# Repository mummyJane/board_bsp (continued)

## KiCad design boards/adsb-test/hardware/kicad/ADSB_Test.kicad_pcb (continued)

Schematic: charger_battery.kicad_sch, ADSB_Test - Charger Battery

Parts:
BT301: CR1220 (optional); Battery_Panasonic_CR1220-VCN_Vertical_CircularHoles; not fitted
C301, C302: 47nF; C_0805_2012Metric_Pad1.18x1.45mm_HandSolder
C303, C304, C305, C306, C307, C310, C311, C312, C313, C314, C316, C317: 10uF 25V; C_0805_2012Metric_Pad1.18x1.45mm_HandSolder
C308, C315: 100nF 25V; C_0805_2012Metric_Pad1.18x1.45mm_HandSolder
C309: 4.7uF 10V; C_0805_2012Metric_Pad1.18x1.45mm_HandSolder
C318: 1nF 50V; C_0805_2012Metric_Pad1.18x1.45mm_HandSolder
C319: 1uF 25V; C_0805_2012Metric_Pad1.18x1.45mm_HandSolder
C320, C321: 1uF; C_0805_2012Metric_Pad1.18x1.45mm_HandSolder
D301: CHG (amber); LED_0805_2012Metric_Pad1.15x1.40mm_HandSolder
D302: BAT43W; D_SOD-123
D303: BAT43W; D_SOD-123; not fitted
J301: 2S Li-ion pack (BAT+, GND, NTC); JST_XH_B3B-XH-A_1x03_P2.50mm_Vertical
L301: 2.2uH; L_Bourns_SRP7028A_7.3x6.6mm
R301: 8.2k 1%; R_0805_2012Metric_Pad1.20x1.40mm_HandSolder
R302: 10k; R_0805_2012Metric_Pad1.20x1.40mm_HandSolder
R303: 5.23k 1%; R_0805_2012Metric_Pad1.20x1.40mm_HandSolder
R304: 30.1k 1%; R_0805_2012Metric_Pad1.20x1.40mm_HandSolder
R305: 100R; R_0805_2012Metric_Pad1.20x1.40mm_HandSolder
R306: 2.2k; R_0805_2012Metric_Pad1.20x1.40mm_HandSolder
RS301, RS302: 20m; R_Shunt_1206_Kelvin_HandSolder
TP301: CHG_QON; TestPoint_Pad_D1.5mm
TP302: BAT_PACK; TestPoint_Pad_D1.5mm
TP303: VSYS; TestPoint_Pad_D1.5mm
TP304: VBUS_CHG; TestPoint_Pad_D1.5mm
TP305: VBACKUP; TestPoint_Pad_D1.5mm
U301: BQ25798; Texas_RQM0029A_VQFN-29_4x4mm_P0.4mm
U302: MCP1703 3.0V (2 uA Iq); SOT-23_Handsoldering

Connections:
/Charger Battery/BKP_CELL: BT301.1 (+), D303.2 (A)
/Charger Battery/CHG_BATP: R305.1, U301.18 (BATP)
/Charger Battery/CHG_BTST1: C301.1, U301.4 (BTST1)
/Charger Battery/CHG_BTST2: C302.1, U301.19 (BTST2)
/Charger Battery/CHG_CE: R302.1, U301.13 (~CE)
/Charger Battery/CHG_LED_A: D301.2 (A), R306.2
/Charger Battery/CHG_PMID: C305.1, C306.1, C307.1, C308.1, U301.29 (PMID)
/Charger Battery/CHG_PROG: R301.1, U301.20 (PROG)
/Charger Battery/CHG_QON: TP301.1, U301.12 (~QON)
/Charger Battery/CHG_REGN: C309.1, R303.1, R306.1, U301.5 (REGN), U301.17 (ILIM_HIZ)
/Charger Battery/CHG_SDRV: C318.1, U301.24 (SDRV)
/Charger Battery/CHG_STAT: D301.1 (K), U301.1 (STAT)
/Charger Battery/CHG_SW1: C301.2, L301.1, U301.28 (SW1)
/Charger Battery/CHG_SW2: C302.2, L301.2, U301.26 (SW2)
/Charger Battery/CHG_TS: J301.3, R303.2, R304.1, U301.16 (TS)
/Charger Battery/VBACKUP_LDO: C320.1, D302.2 (A), U302.2 (VO)
/Charger Battery/VBAT_CHG: C316.1, C317.1, RS301.1, U301.22 (BAT), U301.23 (BAT)
/Charger Battery/VSYS_CHG: C310.1, C311.1, C312.1, C313.1, C314.1, C315.1, RS302.1, U301.25 (SYS)
BAT_PACK: J301.1, R305.2, RS301.4, TP302.1
CHG_PD_INT: U301.21 (~INT); also elsewhere on the board
GND: BT301.2 (-), C303.2, C304.2, C305.2, C306.2, C307.2, C308.2, C309.2, C310.2, C311.2, C312.2, C313.2, C314.2, C315.2, C316.2, C317.2, C318.2, C319.2, C320.2, C321.2, J301.2, R301.2, R302.2, R304.2, U301.10 (ACDRV2), U301.11 (ACDRV1), U301.27 (GND), U302.1 (GND); also elsewhere on the board
I2C_SCL: U301.14 (SCL); also elsewhere on the board
I2C_SDA: U301.15 (SDA); also elsewhere on the board
PM1_CH2_N: RS301.3; also elsewhere on the board
PM1_CH2_P: RS301.2; also elsewhere on the board
PM1_CH3_N: RS302.3; also elsewhere on the board
PM1_CH3_P: RS302.2; also elsewhere on the board
VBACKUP: C321.1, D302.1 (K), D303.1 (K), TP305.1; also elsewhere on the board
VBUS_CHG: C303.1, C304.1, TP304.1, U301.2 (VBUS), U301.3 (VBUS), U301.8 (VAC2), U301.9 (VAC1); also elsewhere on the board
VSYS: C319.1, RS302.4, TP303.1, U302.3 (VI); also elsewhere on the board

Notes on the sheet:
CHARGER: BQ25798 buck-boost 2S charger + power path (I2C 0x6B), PROG 8.2k = 2S / 750 kHz, TS divider 5.23k/30.1k (10k NTC). Pack: 2 x 18650 with its own 2S protection + balancing on J301. RS301 VBAT (PM1 CH2, bidirectional), RS302 VSYS (PM1 CH3). VBACKUP: MCP1703 3.0 V (2 uA) from VSYS -> BAT43W ->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

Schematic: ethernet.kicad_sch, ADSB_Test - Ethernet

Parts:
C801, C803: 10uF; C_1206_3216Metric_Pad1.33x1.80mm_HandSolder
C802, C804, C805: 100nF; C_0805_2012Metric_Pad1.18x1.45mm_HandSolder
C806: 1uF; C_0805_2012Metric_Pad1.18x1.45mm_HandSolder
C807: 470pF; C_0805_2012Metric_Pad1.18x1.45mm_HandSolder
C808, C809: 27pF; C_0805_2012Metric_Pad1.18x1.45mm_HandSolder
C810: 22nF; C_0805_2012Metric_Pad1.18x1.45mm_HandSolder
FB801: 600R@100MHz; L_0805_2012Metric_Pad1.05x1.20mm_HandSolder
J801: HR911105A; RJ45_Hanrun_HR911105A_Horizontal
R801: 12.1k 1%; R_0805_2012Metric_Pad1.20x1.40mm_HandSolder
R802, R803, R804, R806, R814, R815, R816: 10k; R_0805_2012Metric_Pad1.20x1.40mm_HandSolder
R805: 1.5k; R_0805_2012Metric_Pad1.20x1.40mm_HandSolder
R807: 33R; R_0805_2012Metric_Pad1.20x1.40mm_HandSolder
R808, R809, R810, R811: 49.9R 1%; R_0805_2012Metric_Pad1.20x1.40mm_HandSolder
R812, R813: 270R; R_0805_2012Metric_Pad1.20x1.40mm_HandSolder
TP801: ETH_REF_CLK; TestPoint_Pad_D1.5mm
TP802: ETH_1V2; TestPoint_Pad_D1.5mm
U801: LAN8720A; VQFN-24-1EP_4x4mm_P0.5mm_EP2.5x2.5mm_HandSolder
Y801: 25MHz; Crystal_SMD_5032-2Pin_5.0x3.2mm_HandSoldering

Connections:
3V3_ETH: C801.1, C802.1, FB801.1, R804.1, R805.1, R806.1, R814.1, R815.1, R816.1, U801.9 (VDDIO); also elsewhere on the board
/Ethernet/ETH_1V2: C806.1, C807.1, TP802.1, U801.6 (VDDCR)
/Ethernet/ETH_AVDD: C803.1, C804.1, C805.1, C810.1, FB801.2, J801.4 (TCT), J801.5 (RCT), R808.1, R809.1, R810.1, R811.1, U801.1 (VDD2A), U801.19 (VDD1A)
/Ethernet/ETH_LED1: R802.1, R812.1, U801.3 (LED1/REGOFF)
/Ethernet/ETH_LED1_K: J801.12, R812.2
/Ethernet/ETH_LED2: R803.1, R813.1, U801.2 (LED2/~INTSEL)
/Ethernet/ETH_LED2_K: J801.9, R813.2
/Ethernet/ETH_RBIAS: R801.1, U801.24 (RBIAS)
/Ethernet/ETH_REFCLKO: R807.1, U801.14 (~INT/REFCLKO)
/Ethernet/ETH_RXER: R804.2, U801.10 (RXER/PHYAD0)
/Ethernet/ETH_RX_N: J801.6 (RD-), R811.2, U801.22 (RXN)
/Ethernet/ETH_RX_P: J801.3 (RD+), R810.2, U801.23 (RXP)
/Ethernet/ETH_TX_N: J801.2 (TD-), R809.2, U801.20 (TXN)
/Ethernet/ETH_TX_P: J801.1 (TD+), R808.2, U801.21 (TXP)
/Ethernet/ETH_XI: C808.1, U801.5 (XTAL1/CLKIN), Y801.1
/Ethernet/ETH_XO: C809.1, U801.4 (XTAL2), Y801.2
ETH_CRS_DV: R816.2, U801.11 (CRS_DV/MODE2); also elsewhere on the board
ETH_MDC: U801.13 (MDC); also elsewhere on the board
ETH_MDIO: R805.2, U801.12 (MDIO); also elsewhere on the board
ETH_PHY_RST: R806.2, U801.15 (~RST); also elsewhere on the board
ETH_REF_CLK: R807.2, TP801.1; also elsewhere on the board
ETH_RXD0: R814.2, U801.8 (RXD0/MODE0); also elsewhere on the board
ETH_RXD1: R815.2, U801.7 (RXD1/MODE1); also elsewhere on the board
ETH_TXD0: U801.17 (TXD0); also elsewhere on the board
ETH_TXD1_BOOT: U801.18 (TXD1); also elsewhere on the board
ETH_TX_EN: U801.16 (TXEN); also elsewhere on the board
GND: C801.2, C802.2, C803.2, C804.2, C805.2, C806.2, C807.2, C808.2, C809.2, C810.2, J801.8, J801.10, J801.11, J801.SH, R801.2, R802.2, R803.2, U801.25 (VSS); also elsewhere on the board

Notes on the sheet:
ETHERNET: LAN8720A 10/100 RMII PHY (replaces the IP101GRI: KiCad symbol, ESP-IDF lan87xx driver, cheap breakouts for Phase 1). 25 MHz crystal; REFCLKO (pin 14) feeds the P4 REF_CLK in (GPIO50) through 33R. Straps: REGOFF=0 (int. 1V2 on), nINTSEL=0 (REFCLKO, 10k pull-down), PHYAD0=1 (address 1), MOD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

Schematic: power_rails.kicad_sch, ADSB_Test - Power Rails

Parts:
C411, C412, C421, C422: 10uF 25V; C_0805_2012Metric_Pad1.18x1.45mm_HandSolder
C413, C415, C423, C425: 100nF; C_0805_2012Metric_Pad1.18x1.45mm_HandSolder
C414, C424: 33nF; C_0805_2012Metric_Pad1.18x1.45mm_HandSolder
C416, C417, C426, C427: 22uF 10V; C_1206_3216Metric_Pad1.33x1.80mm_HandSolder
C430, C431, C432, C433: 1nF; C_0805_2012Metric_Pad1.18x1.45mm_HandSolder
L411, L421: 4.7uH; L_Bourns_SRP5030T
R411: 100k; R_0805_2012Metric_Pad1.20x1.40mm_HandSolder
R412: 28k; R_0805_2012Metric_Pad1.20x1.40mm_HandSolder
R413: 52.3k 1%; R_0805_2012Metric_Pad1.20x1.40mm_HandSolder
R414, R424: 10k 1%; R_0805_2012Metric_Pad1.20x1.40mm_HandSolder
R423: 31.6k 1%; R_0805_2012Metric_Pad1.20x1.40mm_HandSolder
R430, R431, R432, R433: 100R; R_0805_2012Metric_Pad1.20x1.40mm_HandSolder
RS401: 30m; R_Shunt_1206_Kelvin_HandSolder
RS402, RS403, RS404: 50m; R_Shunt_1206_Kelvin_HandSolder
RS405: 330m; R_Shunt_1206_Kelvin_HandSolder
RS406, RS407: 1R; R_Shunt_1206_Kelvin_HandSolder
RS408, RS409: 2.2R; R_Shunt_1206_Kelvin_HandSolder
SW401: POWER (slide); SW_Slide_SPDT_Angled_CK_OS102011MA1Q
TP401: 5V; TestPoint_Pad_D1.5mm
TP402: 3V3; TestPoint_Pad_D1.5mm
TP403: VSYS; TestPoint_Pad_D1.5mm
TP410: 5V_SDR; TestPoint_Pad_D1.5mm
TP411: 5V_LCD; TestPoint_Pad_D1.5mm
TP412: 3V3_MCU; TestPoint_Pad_D1.5mm
TP413: 3V3_SD; TestPoint_Pad_D1.5mm
TP414: 3V3_ETH; TestPoint_Pad_D1.5mm
TP415: 3V3_GPS; TestPoint_Pad_D1.5mm
TP416: 3V3_M1421; TestPoint_Pad_D1.5mm
TP417: 3V3_PERIPH; TestPoint_Pad_D1.5mm
U411, U421: TPS62933; SOT-583-8_HandSolder
U430, U431, U432, U433: TPS22917; SOT-23-6_Handsoldering

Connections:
3V3: RS401.4, RS404.1, RS405.1, RS406.1, RS407.1, RS408.1, RS409.1, TP402.1; also elsewhere on the board
3V3_BUCK: C426.1, C427.1, L421.2, R423.1, RS401.1
3V3_ETH: R431.2, TP414.1, U431.6 (VOUT); also elsewhere on the board
3V3_GPS: R432.2, TP415.1, U432.6 (VOUT); also elsewhere on the board
3V3_M1421: R433.2, TP416.1, U433.6 (VOUT); also elsewhere on the board
3V3_MCU: RS404.4, TP412.1; also elsewhere on the board
3V3_PERIPH: RS409.4, TP417.1; also elsewhere on the board
3V3_SD: RS405.4, TP413.1; also elsewhere on the board
5V: C416.1, C417.1, L411.2, R413.1, RS402.1, RS403.1, TP401.1
5V_LCD: R430.2, TP411.1, U430.6 (VOUT); also elsewhere on the board
5V_SDR: RS402.4, TP410.1; also elsewhere on the board
/Power Rails/3V3_ETH_SH: RS406.4, U431.1 (VIN)
/Power Rails/3V3_GPS_SH: RS407.4, U432.1 (VIN)
/Power Rails/3V3_M1421_SH: RS408.4, U433.1 (VIN)
/Power Rails/5V_LCD_SH: RS403.4, U430.1 (VIN)
/Power Rails/B3V3_BST: C425.1, U421.6 (BST)
/Power Rails/B3V3_FB: R423.2, R424.1, U421.8 (FB)
/Power Rails/B3V3_SS: C424.1, U421.7 (SS)
/Power Rails/B3V3_SW: C425.2, L421.1, U421.5 (SW)
/Power Rails/B5V_BST: C415.1, U411.6 (BST)
/Power Rails/B5V_FB: R413.2, R414.1, U411.8 (FB)
/Power Rails/B5V_SS: C414.1, U411.7 (SS)
/Power Rails/B5V_SW: C415.2, L411.1, U411.5 (SW)
/Power Rails/CT30: C430.1, U430.4 (CT)
/Power Rails/CT31: C431.1, U431.4 (CT)
/Power Rails/CT32: C432.1, U432.4 (CT)
/Power Rails/CT33: C433.1, U433.4 (CT)
/Power Rails/PWR_EN: R411.2, R412.1, SW401.2 (B), U411.2 (EN), U421.2 (EN)
/Power Rails/QD30: R430.1, U430.5 (QOD)
/Power Rails/QD31: R431.1, U431.5 (QOD)
/Power Rails/QD32: R432.1, U432.5 (QOD)
/Power Rails/QD33: R433.1, U433.5 (QOD)
EXP_EN_ETH: U431.3 (ON); also elsewhere on the board
EXP_EN_GPS: U432.3 (ON); also elsewhere on the board
EXP_EN_LCD: U430.3 (ON); also elsewhere on the board
EXP_EN_M1421: U433.3 (ON); also elsewhere on the board
GND: C411.2, C412.2, C413.2, C414.2, C416.2, C417.2, C421.2, C422.2, C423.2, C424.2, C426.2, C427.2, C430.2, C431.2, C432.2, C433.2, R412.2, R414.2, R424.2, SW401.3 (C), U411.4 (GND), U421.4 (GND), U430.2 (GND), U431.2 (GND), U432.2 (GND), U433.2 (GND); also elsewhere on the board
PM1_CH4_N: RS402.3; also elsewhere on the board
PM1_CH4_P: RS402.2; also elsewhere on the board
PM2_CH1_N: RS403.3; also elsewhere on the board
PM2_CH1_P: RS403.2; also elsewhere on the board
PM2_CH2_N: RS404.3; also elsewhere on the board
PM2_CH2_P: RS404.2; also elsewhere on the board
PM2_CH3_N: RS405.3; also elsewhere on the board
PM2_CH3_P: RS405.2; also elsewhere on the board
PM2_CH4_N: RS406.3; also elsewhere on the board
PM2_CH4_P: RS406.2; also elsewhere on the board
PM3_CH1_N: RS407.3; also elsewhere on the board
PM3_CH1_P: RS407.2; also elsewhere on the board
PM3_CH2_N: RS408.3; also elsewhere on the board
PM3_CH2_P: RS408.2; also elsewhere on the board
PM3_CH3_N: RS409.3; also elsewhere on the board
PM3_CH3_P: RS409.2; also elsewhere on the board
PM3_CH4_N: RS401.3; also elsewhere on the board
PM3_CH4_P: RS401.2; also elsewhere on the board
VSYS: C411.1, C412.1, C413.1, C421.1, C422.1, C423.1, R411.1, TP403.1, U411.3 (VIN), U421.3 (VIN); also elsewhere on the board

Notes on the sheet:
RAILS: two TPS62933 bucks from VSYS (5 V and 3V3, 3 A each), shared PWR_EN with UVLO ~5.5 V. Every branch has a Kelvin shunt (PAC1954 channel on its sense labels) that doubles as a bring-up link. TPS22917 load switches on 5V_LCD, 3V3_ETH, 3V3_GPS, 3V3_M1421 (enabled from the TCA6408A). 3V3_MCU feed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
POWER: SW401 OFF = PWR_EN low = both bucks off. VSYS, charger and VBACKUP stay alive.

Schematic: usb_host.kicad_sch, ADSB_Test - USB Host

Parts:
C1101: 10nF; C_0805_2012Metric_Pad1.18x1.45mm_HandSolder
C1102: 1uF; C_0805_2012Metric_Pad1.18x1.45mm_HandSolder
C1103: 150uF 10V; CP_Elec_6.3x5.8
C1104: 100nF; C_0805_2012Metric_Pad1.18x1.45mm_HandSolder
J1101: USB-A (SDR hub); USB_A_Wuerth_614004134726_Horizontal
R1101: 604R 1%; R_0805_2012Metric_Pad1.20x1.40mm_HandSolder
R1102: 402k 1%; R_0805_2012Metric_Pad1.20x1.40mm_HandSolder
R1103: 10k; R_0805_2012Metric_Pad1.20x1.40mm_HandSolder
R1104: 100k; R_0805_2012Metric_Pad1.20x1.40mm_HandSolder
TP1101: VBUS_HOST; TestPoint_Pad_D1.5mm
TP1102: USBA_FAULT; TestPoint_Pad_D1.5mm
U1101: TPS259621DDA; TI_SO-PowerPAD-8_ThermalVias
U1102: USBLC6-2SC6; SOT-23-6_Handsoldering

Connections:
3V3: R1103.1; also elsewhere on the board
5V_SDR: C1102.1, U1101.4 (VIN); also elsewhere on the board
/USB Host/USBA_DVDT: C1101.1, U1101.2 (dV/dT)
/USB Host/USBA_ILM: R1101.1, U1101.7 (ILM)
/USB Host/USBA_OVC: R1102.1, U1101.8 (OVLO/OVCSEL)
EXP_USBA_EN: R1104.1, U1101.3 (EN/UVLO); also elsewhere on the board
GND: C1101.2, C1102.2, C1103.2, C1104.2, J1101.4 (GND), J1101.SH (Shield), R1101.2, R1102.2, R1104.2, U1101.1 (GND), U1101.9 (GND), U1102.2 (GND); also elsewhere on the board
USBA_FAULT: R1103.2, TP1102.1, U1101.6 (~FLT); also elsewhere on the board
USB_HS_D_N: J1101.2 (D-), U1102.3 (I/O2), U1102.4 (I/O2); also elsewhere on the board
USB_HS_D_P: J1101.3 (D+), U1102.1 (I/O1), U1102.6 (I/O1); also elsewhere on the board
VBUS_HOST: C1103.1, C1104.1, J1101.1 (VBUS), TP1101.1, U1101.5 (OUT), U1102.5 (VBUS)

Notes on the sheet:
USB HOST: P4 HS OTG (module pads 44/45) -> USBLC6 -> USB-A, 90R differential, short. VBUS: 5V_SDR (shunt RS402, PM1 CH4) -> TPS259621 eFuse (~1.5 A, 5.7 V clamp, dV/dt 10 nF) -> 150 uF. EN from the expander (EXP_USBA_EN, 100k pull-down: off at reset), FAULT (open drain) -> P4 GPIO27. PowerPAD: ther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

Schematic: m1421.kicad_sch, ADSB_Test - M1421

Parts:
C1401: 1uF; C_0805_2012Metric_Pad1.18x1.45mm_HandSolder
C1402: 100nF; C_0805_2012Metric_Pad1.18x1.45mm_HandSolder
D1401: RED 1090; LED_0805_2012Metric_Pad1.15x1.40mm_HandSolder
D1402: GREEN UAT; LED_0805_2012Metric_Pad1.15x1.40mm_HandSolder
D1403: ESD7351XV2T1G; D_SOD-523
J1401: m1421 JTAG (J-Link); PinHeader_2x05_P1.27mm_Vertical_SMD
J1402: ADSBee 1421 Dev Kit; PinHeader_1x06_P2.54mm_Vertical
J1403: SMA 1090/978; SMA_Samtec_SMA-J-P-H-ST-EM1_EdgeMount
R1401, R1402, R1403, R1404, R1405, R1409: 100k; R_0805_2012Metric_Pad1.20x1.40mm_HandSolder
R1406: 287R; R_0805_2012Metric_Pad1.20x1.40mm_HandSolder
R1407: 115R; R_0805_2012Metric_Pad1.20x1.40mm_HandSolder
R1408: 100R; R_0805_2012Metric_Pad1.20x1.40mm_HandSolder
SH1401: RF can frame (DNP); Laird_Technologies_BMI-S-203-F_26.21x26.21mm; MPN Laird BMI-S-203-F frame + BMI-S-203-C l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; not fitted
TP1401: SD23; TestPoint_Pad_D1.5mm
TP1402: SD24; TestPoint_Pad_D1.5mm
TP1403: SD25; TestPoint_Pad_D1.5mm
TP1404: LD11; TestPoint_Pad_D1.5mm
TP1405: LD09; TestPoint_Pad_D1.5mm
TP1406: LD08; TestPoint_Pad_D1.5mm
TP1407: LRST; TestPoint_Pad_D1.5mm
TP1408: CSMI; TestPoint_Pad_D1.5mm
TP1409: CSMO; TestPoint_Pad_D1.5mm
TP1410: CSCK; TestPoint_Pad_D1.5mm
TP1411: LRCS; TestPoint_Pad_D1.5mm
TP1412: LBSY; TestPoint_Pad_D1.5mm
U1401: ADSBee m1421; PantsForBirds_ADSBee_m1421_Module_HandSolder
U1402: 74LVC1G97 (AND); SOT-23-6_Handsoldering
U1403: 74LVC1G32; SOT-23-5_HandSoldering
U1404: 74LVC1G07; SOT-23-5_HandSoldering
U1405: SCN-2-11+; MiniCircuits_SCN

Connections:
3V3_M1421: C1401.1, C1402.1, J1401.1 (VTref), J1402.1, R1401.1, R1404.1, R1405.1, R1409.1, U1401.1 (VCC), U1401.4 (VCC), U1401.19 (VCC), U1401.22 (VCC), U1402.5 (VCC), U1403.5 (VCC), U1404.5 (VCC); also elsewhere on the board
/M1421/LED_SD26_A: D1401.2 (A), R1406.2
/M1421/LED_SD27_A: D1402.2 (A), R1407.2
/M1421/M1421_CSCK: TP1410.1, U1401.31 (COPRO_SPI_CLK)
/M1421/M1421_CSMI: TP1408.1, U1401.29 (COPRO_SPI_MISO)
/M1421/M1421_CSMO: TP1409.1, U1401.30 (COPRO_SPI_MOSI)
/M1421/M1421_LBSY: TP1412.1, U1401.33 (LR_BUSY)
/M1421/M1421_LD08: TP1406.1, U1401.5 (LR_DIO8)
/M1421/M1421_LD09: TP1405.1, U1401.3 (LR_DIO9)
/M1421/M1421_LD11: TP1404.1, U1401.2 (LR_DIO11)
/M1421/M1421_LRCS: TP1411.1, U1401.32 (~LR_CS)
/M1421/M1421_LRST: TP1407.1, U1401.7 (~LR_RESET)
/M1421/M1421_RF_978: R1408.2, U1401.24 (SUBG_RF), U1405.6 (P1)
/M1421/M1421_RF_1090: R1408.1, U1401.26 (LR_RF_LF), U1405.4 (P2)
/M1421/M1421_SD23: TP1401.1, U1401.12 (SUBG_DIO23)
/M1421/M1421_SD24: TP1402.1, U1401.13 (SUBG_DIO24)
/M1421/M1421_SD25: TP1403.1, U1401.14 (SUBG_DIO25)
/M1421/M1421_TCKC: J1401.4 (SWCLK/TCK), U1401.9 (JTAG_TCKC)
/M1421/M1421_TDI: J1401.8 (NC/TDI), U1401.11 (JTAG_TDI)
/M1421/M1421_TDO: J1401.6 (SWO/TDO), U1401.10 (JTAG_TDO)
/M1421/M1421_TMSC: J1401.2 (SWDIO/TMS), U1401.8 (JTAG_TMSC)
/M1421/RF_ADSB_ANT: D1403.1 (A1), J1403.1 (In), U1405.2 (SUM)
DEV_M1421_NRST: R1404.2, U1404.2; also elsewhere on the board
DEV_M1421_SYNC: R1403.1, U1403.2; also elsewhere on the board
DEV_M1421_TX: R1401.2, U1402.3 (IN0); also elsewhere on the board
GND: C1401.2, C1402.2, D1401.1 (K), D1402.1 (K), D1403.2 (A2), J1401.3 (GND), J1401.5 (GND), J1401.9 (GNDDetect), J1402.6, J1403.2 (Ext), R1402.2, R1403.2, SH1401.1, U1401.6 (GND), U1401.18 (GND), U1401.23 (GND), U1401.25 (GND), U1401.27 (GND), U1401.34 (GND), U1401.36 (GND), U1401.MP, U1402.1 (IN1), U1402.2 (GND), U1403.3 (GND), U1404.3 (GND), U1405.1 (GND), U1405.3 (GND), U1405.5 (GND); also elsewhere on the board
M1421_NRST: J1401.10 (~RESET), J1402.5, R1405.2, U1401.17 (~SUBG_RESET), U1404.4; also elsewhere on the board
M1421_SD26: R1406.1, U1401.15 (SUBG_DIO26); also elsewhere on the board
M1421_SD27: R1407.1, U1401.16 (SUBG_DIO27); also elsewhere on the board
M1421_SURX: J1402.2, U1401.20 (SUBG_UART_RX), U1402.4 (Y); also elsewhere on the board
M1421_SUTX: J1402.3, U1401.21 (SUBG_UART_TX); also elsewhere on the board
M1421_SYNC: J1402.4, R1402.1, U1401.28 (SYNC), U1403.4; also elsewhere on the board
P4_M1421_SYNC: U1403.1; also elsewhere on the board
P4_M1421_TX: R1409.2, U1402.6 (IN2); also elsewhere on the board

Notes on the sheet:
FIT OPTIONS: solder U1401 (m1421), or leave it off and plug the ADSBee 1421 Dev Kit into J1402 (JST-GH harness, own antenna). SYNC (pad 28) is an INPUT: high at reset = ROM bootloader, high at run time = sleep. SURX = P4 TX AND Dev TX (U1402). M1421_NRST: TCA6408A bit 7 (open-drain style), U1404 fo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

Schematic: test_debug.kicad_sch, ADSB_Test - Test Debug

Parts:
H1601, H1602, H1603, H1604: M2.5; MountingHole_2.7mm_M2.5_Pad_Via
J1601: Kingst LA5016 (2x20 keyed); IDC-Header_2x20_P2.54mm_Vertical
R1601, R1602, R1603, R1604, R1605, R1606, R1607, R1608, R1609, R1610, R1611, R1612, R1613, R1614, R1615, R1616: 100R; R_0805_2012Metric_Pad1.20x1.40mm_HandSolder
R1617: 0R; R_0805_2012Metric_Pad1.20x1.40mm_HandSolder; not fitted
TP1601: LA_PWM1; TestPoint_Pad_D1.5mm
TP1602: LA_PWM2; TestPoint_Pad_D1.5mm
TP1603, TP1604, TP1605, TP1606: GND; TestPoint_Pad_D1.5mm

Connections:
/Test Debug/LA_CH0: J1601.1, R1601.2
/Test Debug/LA_CH1: J1601.3, R1602.2
/Test Debug/LA_CH2: J1601.5, R1603.2
/Test Debug/LA_CH3: J1601.7, R1604.2
/Test Debug/LA_CH4: J1601.9, R1605.2
/Test Debug/LA_CH5: J1601.11, R1606.2
/Test Debug/LA_CH6: J1601.13, R1607.2
/Test Debug/LA_CH7: J1601.15, R1608.2
/Test Debug/LA_CH8: J1601.19, R1609.2
/Test Debug/LA_CH9: J1601.21, R1610.2
/Test Debug/LA_CH10: J1601.23, R1611.2
/Test Debug/LA_CH11: J1601.25, R1612.2
/Test Debug/LA_CH12: J1601.27, R1613.2
/Test Debug/LA_CH13: J1601.29, R1614.2
/Test Debug/LA_CH14: J1601.31, R1615.2
/Test Debug/LA_CH15: J1601.33, R1616.2
/Test Debug/LA_PWM1: J1601.37, R1617.1, TP1601.1
/Test Debug/LA_PWM2: J1601.39, TP1602.1
C5_CON_TX: R1610.1; also elsewhere on the board
CHG_PD_INT: R1614.1; also elsewhere on the board
DBG_A: R1615.1; also elsewhere on the board
DBG_B: R1616.1; also elsewhere on the board
GND: H1601.1, H1602.1, H1603.1, H1604.1, J1601.17, J1601.18, J1601.35, J1601.36, TP1603.1, TP1604.1, TP1605.1, TP1606.1; also elsewhere on the board
GPS_PPS: R1603.1, R1617.2; also elsewhere on the board
GPS_TX: R1604.1; also elsewhere on the board
I2C_SCL: R1601.1; also elsewhere on the board
I2C_SDA: R1602.1; also elsewhere on the board
M1421_SD26: R1608.1; also elsewhere on the board
M1421_SD27: R1612.1; also elsewhere on the board
M1421_SURX: R1606.1; also elsewhere on the board
M1421_SUTX: R1605.1; also elsewhere on the board
M1421_SYNC: R1607.1; also elsewhere on the board
P4_CON_TX: R1609.1; also elsewhere on the board
P4_USER_TX: R1611.1; also elsewhere on the board
PM_ALERT: R1613.1; also elsewhere on the board

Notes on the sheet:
LOGIC ANALYSER: Kingst LA5016 40-way cable into J1601. Key-side row (odd pins): 1-15 CH0-7, 17 GND, 19-33 CH8-15, 35 GND, 37 PWM1, 39 PWM2 (LA outputs). Even row reserved for the LA5032 (18/36 GND). CH: 0 SCL, 1 SDA, 2 GPS PPS, 3 GPS TX, 4 m1421 SUTX, 5 m1421 SURX, 6 SYNC, 7 SD26 | 8 P4 console TX,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

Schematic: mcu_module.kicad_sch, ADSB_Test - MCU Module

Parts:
C601, C602: 22uF 10V; C_1206_3216Metric_Pad1.33x1.80mm_HandSolder
C603, C608, C609: 100nF; C_0805_2012Metric_Pad1.18x1.45mm_HandSolder
C604, C607: 1uF; C_0805_2012Metric_Pad1.18x1.45mm_HandSolder
C605, C606: 22pF; C_0805_2012Metric_Pad1.18x1.45mm_HandSolder
J601: U.FL Wi-Fi (from module IPEX); U.FL_Hirose_U.FL-R-SMT-1_Vertical
J602: RP-SMA Wi-Fi 2.4/5 GHz; SMA_Molex_73251-3152_RP_EdgeMount; MPN Molex 0732513152 (RP-SMA, jam nut); foo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
R601: 10M; R_0805_2012Metric_Pad1.20x1.40mm_HandSolder
R602, R603: 2.2k; R_0805_2012Metric_Pad1.20x1.40mm_HandSolder
R604: 4.7k; R_0805_2012Metric_Pad1.20x1.40mm_HandSolder
R605, R607, R608: 10k; R_0805_2012Metric_Pad1.20x1.40mm_HandSolder
R606: 330R; R_0805_2012Metric_Pad1.20x1.40mm_HandSolder
R609: 470R; R_0805_2012Metric_Pad1.20x1.40mm_HandSolder
SW601: BOOT; SW_PUSH_6mm
SW602: RESET; SW_PUSH_6mm
SW603: SLEEP/WAKE; SW_Tactile_SPST_Angled_PTS645Vx31-2LFS
TP601: C5_IO27; TestPoint_Pad_D1.5mm
TP602: C5_IO25; TestPoint_Pad_D1.5mm
TP603: C5_IO24; TestPoint_Pad_D1.5mm
TP604: C5_IO23; TestPoint_Pad_D1.5mm
TP605: C5_IO6; TestPoint_Pad_D1.5mm
TP606: C5_IO5; TestPoint_Pad_D1.5mm
TP607: C5_IO4; TestPoint_Pad_D1.5mm
TP608: SLEEP_WAKE; TestPoint_Pad_D1.5mm
TP609: P4_GPIO20; TestPoint_Pad_D1.5mm
TP610: P4_GPIO36; TestPoint_Pad_D1.5mm
TP611: C5_PU; TestPoint_Pad_D1.5mm
U601: ESP32-P4C5 Core (OSPTEK); OSPTEK_ESP32-P4C5_Core_HandSolder
Y601: 32.768kHz; Crystal_C26-LF_D2.1mm_L6.5mm_Horizontal

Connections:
3V3: R602.1, R603.1, R604.1, R605.1; also elsewhere on the board
3V3_MCU: C601.1, C602.1, C603.1, R607.1, R608.1, U601.85 (ESP_3V3), U601.86 (ESP_3V3); also elsewhere on the board
/MCU Module/C5_IO4: TP607.1, U601.14 (C5_IO4)
/MCU Module/C5_IO5: TP606.1, U601.13 (C5_IO5)
/MCU Module/C5_IO6: TP605.1, U601.12 (C5_IO6)
/MCU Module/C5_IO23: TP604.1, U601.11 (C5_IO23)
/MCU Module/C5_IO24: TP603.1, U601.10 (C5_IO24)
/MCU Module/C5_IO25: TP602.1, U601.9 (C5_IO25)
/MCU Module/C5_IO26: R605.2, U601.8 (C5_IO26)
/MCU Module/C5_IO27: TP601.1, U601.7 (C5_IO27)
/MCU Module/C5_PU: R606.1, TP611.1, U601.82 (GPIO54/C5_CHIP_PU)
/MCU Module/P4_GPIO20: TP609.1, U601.29 (GPIO20)
/MCU Module/P4_GPIO36: TP610.1, U601.63 (GPIO36)
/MCU Module/SLEEP_BTN: R608.2, R609.1, SW603.1
/MCU Module/SLEEP_WAKE: C609.1, R609.2, TP608.1, U601.27 (GPIO12)
/MCU Module/WIFI_ANT: J601.1 (In), J602.1 (In)
/MCU Module/XTAL32_N: C606.1, R601.2, U601.88 (GPIO0/XTAL_32K_N), Y601.2
/MCU Module/XTAL32_P: C605.1, R601.1, U601.16 (GPIO1/XTAL_32K_P), Y601.1
C5_BOOT: U601.6 (C5_IO28/BOOT); also elsewhere on the board
C5_CON_RX: U601.4 (C5_U0RXD); also elsewhere on the board
C5_CON_TX: U601.5 (C5_U0TXD); also elsewhere on the board
C5_EN: R606.2; also elsewhere on the board
CHG_PD_INT: U601.24 (GPIO9); also elsewhere on the board
DBG_A: U601.25 (GPIO10); also elsewhere on the board
DBG_B: U601.26 (GPIO11); also elsewhere on the board
DSI_CLK_N: U601.36 (DSI_CLKN); also elsewhere on the board
DSI_CLK_P: U601.37 (DSI_CLKP); also elsewhere on the board
DSI_D0_N: U601.39 (DSI_D0N); also elsewhere on the board
DSI_D0_P: U601.38 (DSI_D0P); also elsewhere on the board
DSI_D1_N: U601.35 (DSI_D1N); also elsewhere on the board
DSI_D1_P: U601.34 (DSI_D1P); also elsewhere on the board
ETH_CRS_DV: U601.55 (GPIO28); also elsewhere on the board
ETH_MDC: U601.58 (GPIO31); also elsewhere on the board
ETH_MDIO: U601.80 (GPIO52); also elsewhere on the board
ETH_PHY_RST: U601.79 (GPIO51); also elsewhere on the board
ETH_REF_CLK: U601.78 (GPIO50); also elsewhere on the board
ETH_RXD0: U601.56 (GPIO29); also elsewhere on the board
ETH_RXD1: U601.57 (GPIO30); also elsewhere on the board
ETH_TXD0: U601.61 (GPIO34); also elsewhere on the board
ETH_TXD1_BOOT: R604.2, SW601.1, U601.62 (GPIO35/BOOT); also elsewhere on the board
ETH_TX_EN: U601.77 (GPIO49); also elsewhere on the board
EXP_INT: U601.81 (GPIO53); also elsewhere on the board
GND: C601.2, C602.2, C603.2, C604.2, C605.2, C606.2, C607.2, C608.2, C609.2, J601.2 (Ext), J602.2 (Ext), SW601.2, SW602.2, SW603.2, U601.1 (GND), U601.3 (GND), U601.15 (GND), U601.33 (GND), U601.40 (GND), U601.47 (GND), U601.52 (GND), U601.83 (GND); also elsewhere on the board
GPS_PPS: U601.19 (GPIO4); also elsewhere on the board
GPS_TX: U601.18 (GPIO3); also elsewhere on the board
I2C_SCL: R603.2, U601.23 (GPIO8); also elsewhere on the board
I2C_SDA: R602.2, U601.22 (GPIO7); also elsewhere on the board
LCD_BL_PWM: U601.59 (GPIO32); also elsewhere on the board
LCD_RST: U601.60 (GPIO33); also elsewhere on the board
M1421_SUTX: U601.75 (GPIO47); also elsewhere on the board
P4_CON_RX: U601.65 (GPIO38/U0RXD); also elsewhere on the board
P4_CON_TX: U601.64 (GPIO37/U0TXD); also elsewhere on the board
P4_EN: C607.1, R607.2, SW602.1, U601.87 (CHIP_PU); also elsewhere on the board
P4_GPS_TX: U601.17 (GPIO2); also elsewhere on the board
P4_M1421_SYNC: U601.76 (GPIO48); also elsewhere on the board
P4_M1421_TX: U601.74 (GPIO46); also elsewhere on the board
P4_USER_RX: U601.31 (GPIO22); also elsewhere on the board
P4_USER_TX: U601.30 (GPIO21); also elsewhere on the board
P4_USJ_D_N: U601.50 (GPIO24/USB_JTAG_N); also elsewhere on the board
P4_USJ_D_P: U601.51 (GPIO25/USB_JTAG_P); also elsewhere on the board
PM_ALERT: U601.20 (GPIO5); also elsewhere on the board
RTC_INT: U601.28 (GPIO13); also elsewhere on the board
SD_CLK: U601.71 (GPIO43); also elsewhere on the board
SD_CMD: U601.72 (GPIO44); also elsewhere on the board
SD_D0: U601.67 (GPIO39); also elsewhere on the board
SD_D1: U601.68 (GPIO40); also elsewhere on the board
SD_D2: U601.69 (GPIO41); also elsewhere on the board
SD_D3: U601.70 (GPIO42); also elsewhere on the board
SD_PWR_EN: U601.73 (GPIO45); also elsewhere on the board
SD_VIO: C604.1, U601.66 (ESP_LDO_VO4); also elsewhere on the board
TOUCH_INT: U601.53 (GPIO26); also elsewhere on the board
TOUCH_RST: U601.32 (GPIO23); also elsewhere on the board
USBA_FAULT: U601.54 (GPIO27); also elsewhere on the board
USB_HS_D_N: U601.48 (USB_DM); also elsewhere on the board
USB_HS_D_P: U601.49 (USB_DP); also elsewhere on the board
VBACKUP: C608.1, U601.84 (RTC_VBAT); also elsewhere on the board

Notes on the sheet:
MCU MODULE: OSPTEK ESP32-P4C5 Core (ESP32-P4 rev v3.x + ESP32-C5HF4, 16 MB flash, 32 MB PSRAM). Inside the module: SDIO on P4 GPIO14-19, C5 CHIP_PU = P4 GPIO54 (pad 82), C5 GPIO2 = P4 GPIO6 (pad 21, NC here) - the same wiring as the Waveshare reference board. Pins: bsp/include/bsp/board_pins.h. 3.3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

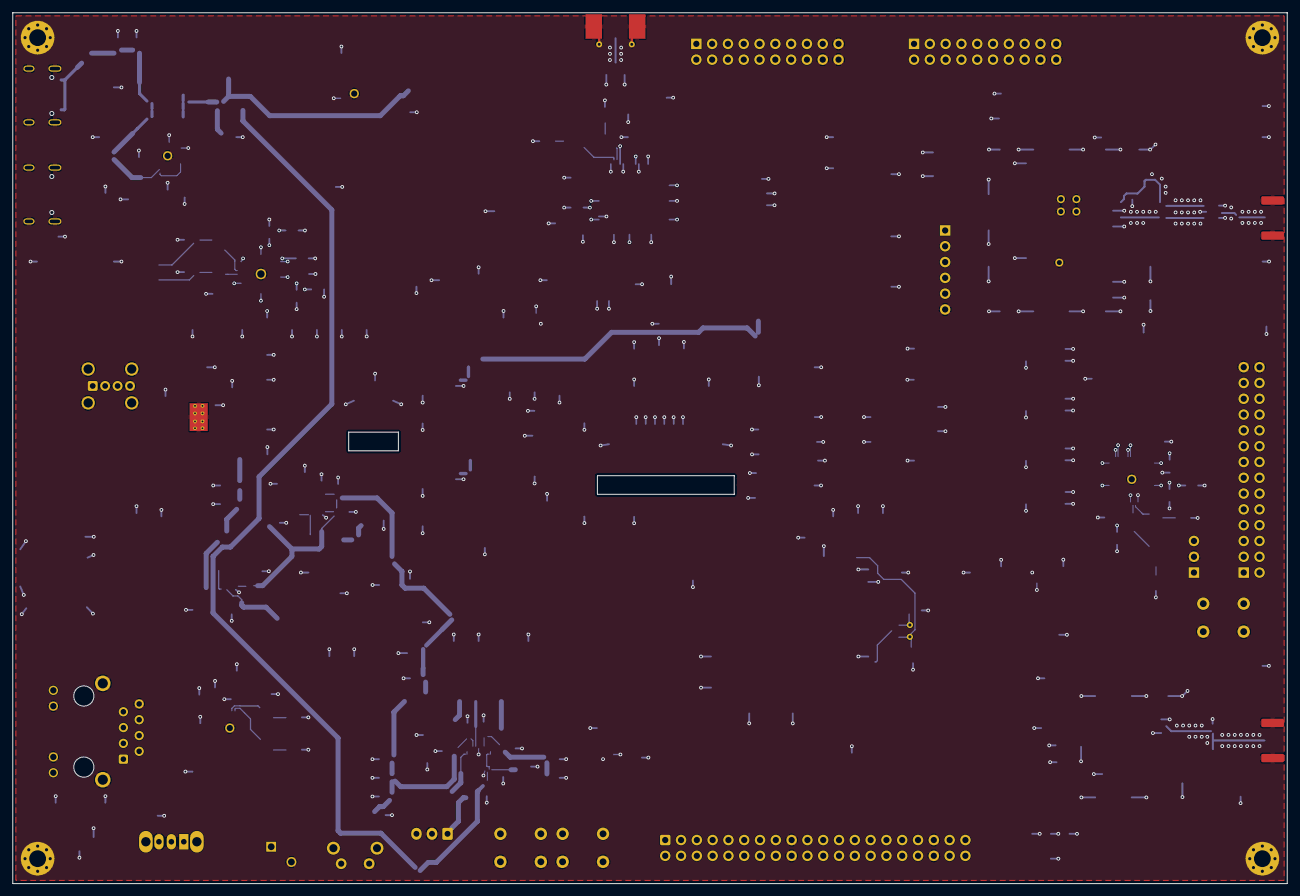
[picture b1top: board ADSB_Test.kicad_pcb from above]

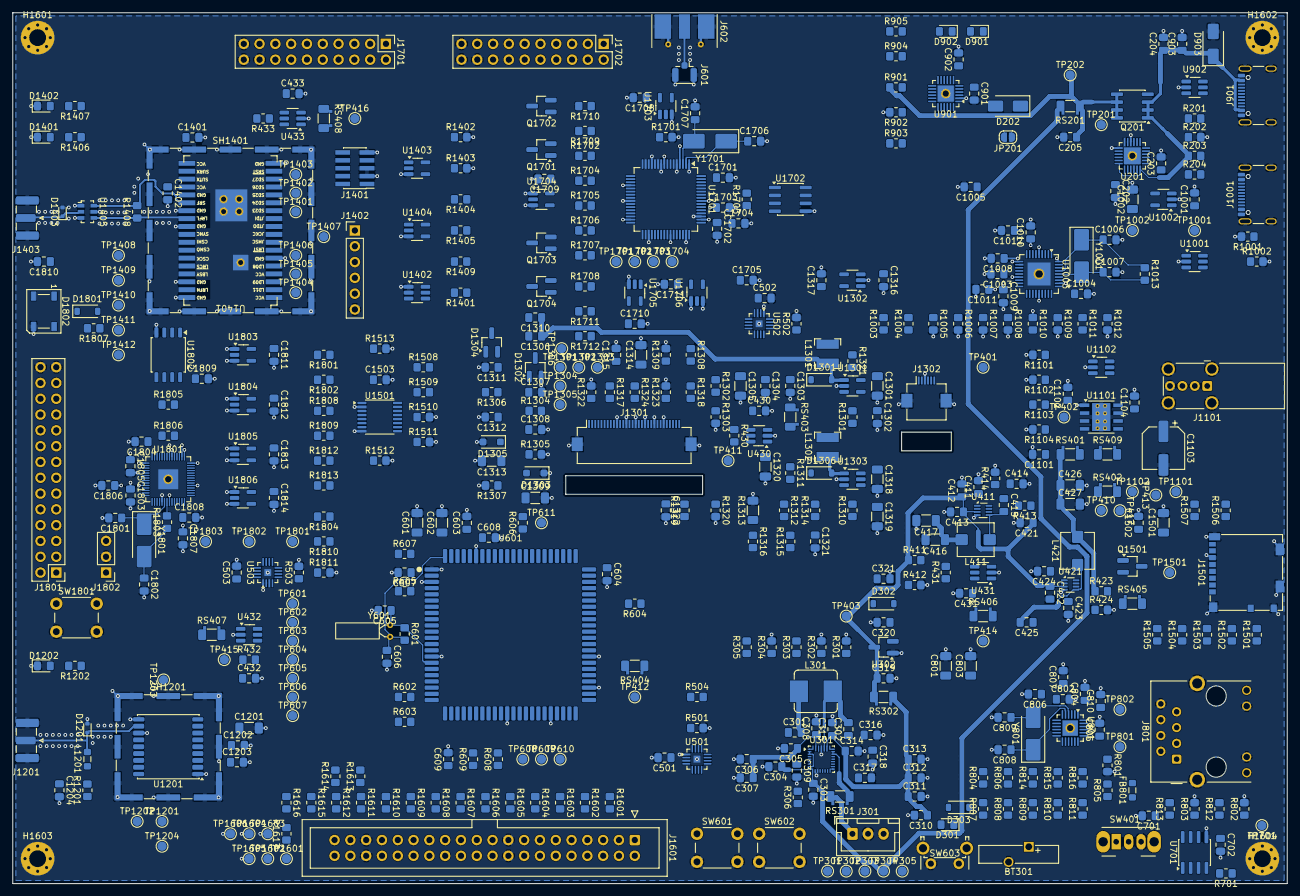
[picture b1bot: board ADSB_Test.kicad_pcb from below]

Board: 4 copper layers, 204.9 x 140.0 mm, 502 parts (502 on the bottom side), 397 nets.

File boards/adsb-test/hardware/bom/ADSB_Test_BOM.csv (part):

line,qty,refs,value,footprint,dnp,manufacturer,mpn,supplier,supplier_pn,order_link,unit_usd,ext_usd,stock_2026_10_12,uk_stock,notes,Mouser UK,Farnell UK,RS UK
1,1,U201,STUSB4500QTR,QFN-24-1EP_4x4mm_P0.5mm_EP2.7x2.7mm_HandSolder,,STMicroelectronics,STUSB4500QTR,DigiKey,497-18060-1-ND,https://www.digikey.com/en/products/result?keywords=STUSB4500QTR,2.22,2.22,27k,,,https://www.mouser.co.uk/c/?q=STUSB4500QTR,https://uk.farnell.com/search?st=STUSB4500QTR,https://uk.rs-online.com/web/c/?searchTerm=STUSB4500QTR
2,1,U301,BQ25798,Texas_RQM0029A_VQFN-29_4x4mm_P0.4mm,,Texas Instruments,BQ25798RQMR,DigiKey,296-BQ25798RQMRCT-ND,https://www.digikey.com/en/products/result?keywords=BQ25798RQMR,5.90,5.90,7.3k,,,https://www.mouser.co.uk/c/?q=BQ25798RQMR,https://uk.farnell.com/search?st=BQ25798RQMR,https://uk.rs-online.com/web/c/?searchTerm=BQ25798RQMR
3,1,U302,MCP1703 3.0V (2 uA Iq),SOT-23_Handsoldering,,Microchip,MCP1703T-3002E/CB,DigiKey,MCP1703T-3002E/CBCT-ND,https://www.digikey.com/en/products/result?keywords=MCP1703T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,0.75,0.75,5.1k,,,https://www.mouser.co.uk/c/?q=MCP1703T-3002E/CB,https://uk.farnell.com/search?st=MCP1703T-3002E/CB,https://uk.rs-online.com/web/c/?searchTerm=MCP1703T-3002E/CB
4,2,U411 U421,TPS62933,SOT-583-8_HandSolder,,Texas Instruments,TPS62933DRLR,DigiKey,296-TPS62933DRLRCT-ND,https://www.digikey.com/en/products/result?keywords=TPS62933DRLR,1.60,3.20,64k,,,https://www.mouser.co.uk/c/?q=TPS62933DRLR,https://uk.farnell.com/search?st=TPS62933DRLR,https://uk.rs-online.com/web/c/?searchTerm=TPS62933DRLR
5,4,U430 U431 U432 U433,TPS22917,SOT-23-6_Handsoldering,,Texas Instruments,TPS22917DBVR,DigiKey,296-50498-1-ND,https://www.digikey.com/en/products/result?keywords=TPS22917DBVR,0.55,2.20,72k,,,https://www.mouser.co.uk/c/?q=TPS22917DBVR,https://uk.farnell.com/search?st=TPS22917DBVR,https://uk.rs-online.com/web/c/?searchTerm=TPS22917DBVR
6,1,U501,PAC1954 (PM1),VQFN-16-1EP_3x3mm_P0.5mm_EP1.1x1.1mm_HandSolder,,Microchip,PAC1954T-E/4MX,DigiKey,150-PAC1954T-E/4MXCT-ND,https://www.digikey.com/en/products/result?keywords=PAC1954T-E/4MX,2.02,2.02,10k,,,https://www.mouser.co.uk/c/?q=PAC1954T-E/4MX,https://uk.farnell.com/search?st=PAC1954T-E/4MX,https://uk.rs-online.com/web/c/?searchTerm=PAC1954T-E/4MX
7,1,U502,PAC1954 (PM2),VQFN-16-1EP_3x3mm_P0.5mm_EP1.1x1.1mm_HandSolder,,Microchip,PAC1954T-E/4MX,DigiKey,150-PAC1954T-E/4MXCT-ND,https://www.digikey.com/en/products/result?keywords=PAC1954T-E/4MX,2.02,2.02,10k,,,https://www.mouser.co.uk/c/?q=PAC1954T-E/4MX,https://uk.farnell.com/search?st=PAC1954T-E/4MX,https://uk.rs-online.com/web/c/?searchTerm=PAC1954T-E/4MX
8,1,U503,PAC1954 (PM3),VQFN-16-1EP_3x3mm_P0.5mm_EP1.1x1.1mm_HandSolder,,Microchip,PAC1954T-E/4MX,DigiKey,150-PAC1954T-E/4MXCT-ND,https://www.digikey.com/en/products/result?keywords=PAC1954T-E/4MX,2.02,2.02,10k,,,https://www.mouser.co.uk/c/?q=PAC1954T-E/4MX,https://uk.farnell.com/search?st=PAC1954T-E/4MX,https://uk.rs-online.com/web/c/?searchTerm=PAC1954T-E/4MX
9,1,U601,ESP32-P4C5 Core (OSPTEK),OSPTEK_ESP32-P4C5_Core_HandSolder,,OSPTEK,ESP32-P4C5 Core module,AliExpress (OSPTEK),https://www.aliexpress.com/item/1005012626312933.html,https://www.aliexpress.com/item/1005012626312933.html,16.50,16.50,,,about GBP 13 (user 2026-10-12); docs github.com/osptek/esp32-p4c5-core-board,,,
10,1,U801,LAN8720A,VQFN-24-1EP_4x4mm_P0.5mm_EP2.5x2.5mm_HandSolder,,Microchip,LAN8720A-CP-TR,DigiKey,LAN8720A-CP-CT-ND,https://www.digikey.com/en/products/result?keywords=LAN8720A-CP-TR,1.03,1.03,35k,,,https://www.mouser.co.uk/c/?q=LAN8720A-CP-TR,https://uk.farnell.com/search?st=LAN8720A-CP-TR,https://uk.rs-online.com/web/c/?searchTerm=LAN8720A-CP-TR
11,1,U901,CP2102N-A02-GQFN24,QFN-24-1EP_4x4mm_P0.5mm_EP2.6x2.6mm_HandSolder,,Silicon Labs,CP2102N-A02-GQFN24R,DigiKey,336-5888-1-ND,https://www.digikey.com/en/products/result?keywords=CP2102N-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,5.46,5.46,10.9k,,,https://www.mouser.co.uk/c/?q=CP2102N-A02-GQFN24R,https://uk.farnell.com/search?st=CP2102N-A02-GQFN24R,https://uk.rs-online.com/web/c/?searchTerm=CP2102N-A02-GQFN24R
12,3,U902 U1001 U1102,USBLC6-2SC6,SOT-23-6_Handsoldering,,STMicroelectronics,USBLC6-2SC6,DigiKey,497-5235-1-ND,https://www.digikey.com/en/products/result?keywords=USBLC6-2SC6,0.54,1.62,127k,,,https://www.mouser.co.uk/c/?q=USBLC6-2SC6,https://uk.farnell.com/search?st=USBLC6-2SC6,https://uk.rs-online.com/web/c/?searchTerm=USBLC6-2SC6
13,1,U1002,AP2112K-3.3,SOT-23-5_HandSoldering,,Diodes Inc,AP2112K-3.3TRG1,DigiKey,AP2112K-3.3TRG1DICT-ND,https://www.digikey.com/en/products/result?keywords=AP2112K-3.3TRG1,0.28,0.28,431k,,,https://www.mouser.co.uk/c/?q=AP2112K-3.3TRG1,https://uk.farnell.com/search?st=AP2112K-3.3TRG1,https://uk.rs-online.com/web/c/?searchTerm=AP2112K-3.3TRG1
14,1,U1003,USB2514B,QFN-36-1EP_6x6mm_P0.5mm_EP3.7x3.7mm_HandSolder,,Microchip,USB2514B-AEZC-TR,DigiKey,USB2514B-AEZC-CT-ND,https://www.digikey.com/en/products/result?keywords=USB2514B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,2.49,2.49,14k,,,https://www.mouser.co.uk/c/?q=USB2514B-AEZC-TR,https://uk.farnell.com/search?st=USB2514B-AEZC-TR,https://uk.rs-online.com/web/c/?searchTerm=USB2514B-AEZC-TR
15,1,U1101,TPS259621DDA,TI_SO-PowerPAD-8_ThermalVias,,Texas Instruments,TPS259621DDAR,DigiKey,296-TPS259621DDARCT-ND,https://www.digikey.com/en/products/result?keywords=TPS259621DDAR,1.07,1.07,1.1k,,,https://www.mouser.co.uk/c/?q=TPS259621DDAR,https://uk.farnell.com/search?st=TPS259621DDAR,https://uk.rs-online.com/web/c/?searchTerm=TPS259621DDAR
16,1,U1201,MAX-M10S,ublox_MAX,,u-blox,MAX-M10S-00B,DigiKey,672-MAX-M10S-00BCT-ND,https://www.digikey.com/en/products/result?keywords=MAX-M10S-00B,11.42,11.42,4.2k,,,https://www.mouser.co.uk/c/?q=MAX-M10S-00B,https://uk.farnell.com/search?st=MAX-M10S-00B,https://uk.rs-online.com/web/c/?searchTerm=MAX-M10S-00B
17,1,U1301,AP3012KTR-E1,SOT-23-5_HandSoldering,,Diodes Inc,AP3012KTR-E1,DigiKey,AP3012KTR-E1DICT-ND,https://www.digikey.com/en/products/result?keywords=AP3012KTR-E1,0.64,0.64,440,,,https://www.mouser.co.uk/c/?q=AP3012KTR-E1,https://uk.farnell.com/search?st=AP3012KTR-E1,https://uk.rs-online.com/web/c/?searchTerm=AP3012KTR-E1
18,1,U1302,AP2112K-1.8,SOT-23-5_HandSoldering,,Diodes Inc,AP2112K-1.8TRG1,DigiKey,AP2112K-1.8TRG1DICT-ND,https://www.digikey.com/en/products/result?keywords=AP2112K-1.8TRG1,0.27,0.27,100k,,,https://www.mouser.co.uk/c/?q=AP2112K-1.8TRG1,https://uk.farnell.com/search?st=AP2112K-1.8TRG1,https://uk.rs-online.com/web/c/?searchTerm=AP2112K-1.8TRG1
19,1,U1303,AP3032KTR-G1,SOT-23-6_Handsoldering,,Diodes Inc,AP3032KTR-G1,DigiKey,AP3032KTR-G1DICT-ND,https://www.digikey.com/en/products/result?keywords=AP3032KTR-G1,0.31,0.31,15,,low stock - order early,https://www.mouser.co.uk/c/?q=AP3032KTR-G1,https://uk.farnell.com/search?st=AP3032KTR-G1,https://uk.rs-online.com/web/c/?searchTerm=AP3032KTR-G1
20,1,U1401,ADSBee m1421,PantsForBirds_ADSBee_m1421_Module_HandSolder,,Pants for Birds,ADSBee m1421,Pants for Birds,https://pantsforbirds.com/adsbee/dual-band-module/,https://pantsforbirds.com/adsbee/dual-band-module/,,,,,Or start with the ADSBee 1421 Dev Kit on J1402,,,
21,1,U1402,74LVC1G97 (AND),SOT-23-6_Handsoldering,,Texas Instruments,SN74LVC1G97DBVR,DigiKey,296-15581-1-ND,https://www.digikey.com/en/products/result?keywords=SN74LVC1G97DBVR,0.23,0.23,24k,,,https://www.mouser.co.uk/c/?q=SN74LVC1G97DBVR,https://uk.farnell.com/search?st=SN74LVC1G97DBVR,https://uk.rs-online.com/web/c/?searchTerm=SN74LVC1G97DBVR
22,1,U1403,74LVC1G32,SOT-23-5_HandSoldering,,Texas Instruments,SN74LVC1G32DBVR,DigiKey,296-9847-1-ND,https://www.digikey.com/en/products/result?keywords=SN74LVC1G32DBVR,0.12,0.12,1.4k,,,https://www.mouser.co.uk/c/?q=SN74LVC1G32DBVR,https://uk.farnell.com/search?st=SN74LVC1G32DBVR,https://uk.rs-online.com/web/c/?searchTerm=SN74LVC1G32DBVR
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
